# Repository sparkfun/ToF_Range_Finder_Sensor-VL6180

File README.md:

SparkFun ToF Range Finder Sensor-VL6180
=========================================

[*SparkFun ToF Range Finder Sensor-VL6180 (SEN-12785)*](https://www.sparkfun.com/products/12785)

This is the SparkFun “Time-of-Flight” Range Finder, a sensor board for the VL6180 distance sensor. 
Unlike most distance sensors that rely on reflected light intensity or reflected angles to determine range, 
the VL6180 uses a precise clock to measure the time it takes light to bounce back from a surface.

Repository Contents
-------------------
* **/Hardware** - All Eagle design files (.brd, .sch)
* **/Libraries** - All Arduino libraries and board examples
* **/Production** - Test bed files and production panel files

Documentation
--------------
* **[Library](https://github.com/sparkfun/SparkFun_ToF_Range_Finder-VL6180_Arduino_Library)** - Arduino library for the VL6180.
* **[Hookup Guide](https://learn.sparkfun.com/tutorials/vl6180-hookup-guide)** - Basic hookup guide for the VL6180.
* **[SparkFun Fritzing repo](https://github.com/sparkfun/Fritzing_Parts)** - Fritzing diagrams for SparkFun products.
* **[SparkFun 3D Model repo](https://github.com/sparkfun/3D_Models)** - 3D models of SparkFun products. 

License Information
-------------------
This product is _**open source**_! 

The **hardware** is released under [Creative Commons ShareAlike 4.0 International](https://creativecommons.org/licenses/by-sa/4.0/).

The **code** is beerware; if you see me (or any other SparkFun employee) at the local, and you've found our code helpful, please buy us a round!

Please use, reuse, and modify these files as you see fit. Please maintain attribution to SparkFun Electronics and release anything derivative under the same license.

Distributed as-is; no warranty is given.

- Your friends at SparkFun.

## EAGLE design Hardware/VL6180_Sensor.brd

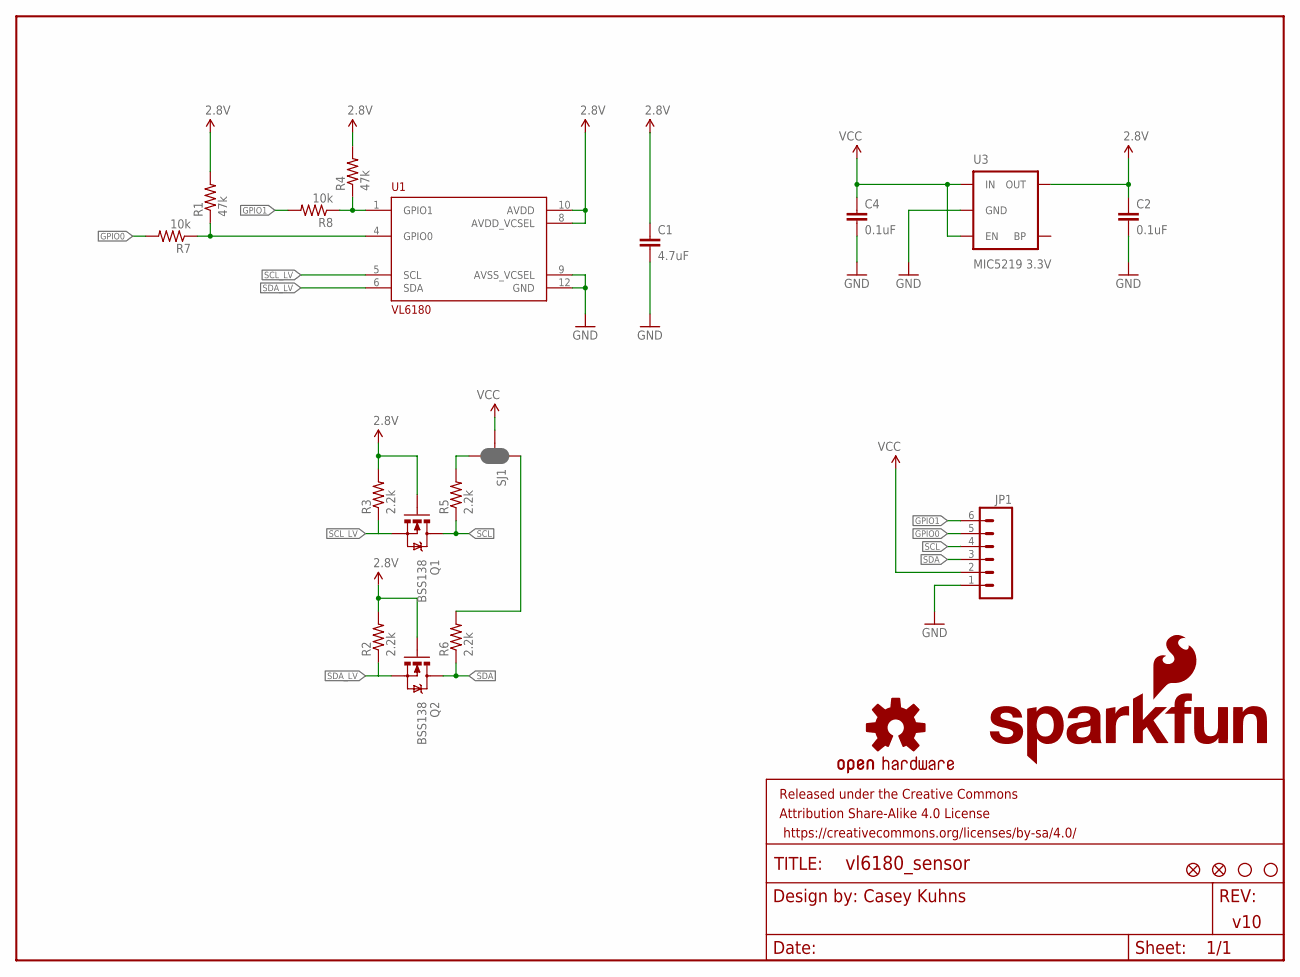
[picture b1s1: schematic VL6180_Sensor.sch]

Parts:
C1: 4.7uF; 0603-CAP
C2, C4: 0.1uF; 0603-CAP
FID1, FID2: FIDUCIAL1X2; FIDUCIAL-1X2
FRAME1: FRAME-LETTER; CREATIVE_COMMONS
JP1: M06SIP; 1X06
LOGO1: SFE_LOGO_NAME_FLAME.1_INCH; SFE_LOGO_NAME_FLAME_.1
LOGO2: OSHW-LOGOS; OSHW-LOGO-S
Q1, Q2: BSS138; SOT23
R1, R4: 47k; 0603-RES
R2, R3, R5, R6: 2.2k; 0603-RES
R7, R8: 10k; 0603-RES
SJ1: JUMPER-PAD-3-NC_BY_PASTE; PAD-JUMPER-3-NC_BY_PASTE_YES_SILK_FULL_BOX
STANDOFF1, STANDOFF2: STAND-OFF
U1: VL6180
U3: MIC5219 3.3V; SOT23-5

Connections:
2.8V: C1.1, C2.1, Q1.1 (G), Q2.1 (G), R1.2, R2.2, R3.2, R4.2, U1.8 (AVDD_VCSEL), U1.10 (AVDD), U3.5 (OUT)
GND: C1.2, C2.2, C4.2, JP1.1, U1.9 (AVSS_VCSEL), U1.12 (GND), U3.2 (GND)
GPIO0: JP1.5, R7.2
GPIO1: JP1.6, R8.2
unnamed: R6.2, SJ1.1
unnamed: R5.2, SJ1.3
unnamed: R1.1, R7.1, U1.4 (GPIO0)
unnamed: R4.1, R8.1, U1.1 (GPIO1)
SCL: JP1.4, Q1.3 (D), R5.1
SCL_LV: Q1.2 (S), R3.1, U1.5 (SCL)
SDA: JP1.3, Q2.3 (D), R6.1
SDA_LV: Q2.2 (S), R2.1, U1.6 (SDA)
VCC: C4.1, JP1.2, SJ1.2, U3.1 (IN), U3.3 (EN)

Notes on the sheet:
Casey Kuhns
v10

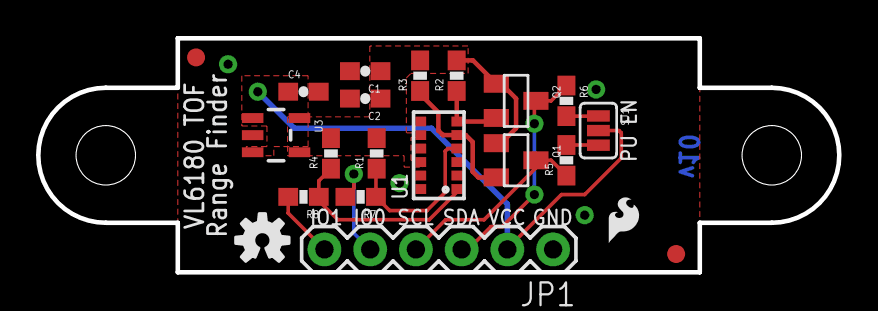
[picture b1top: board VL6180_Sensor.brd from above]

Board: 2 copper layers, 44.5 x 13.0 mm, 25 parts (1 on the bottom side), 13 nets.

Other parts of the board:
U$2: SFE_LOGO_FLAME_.1

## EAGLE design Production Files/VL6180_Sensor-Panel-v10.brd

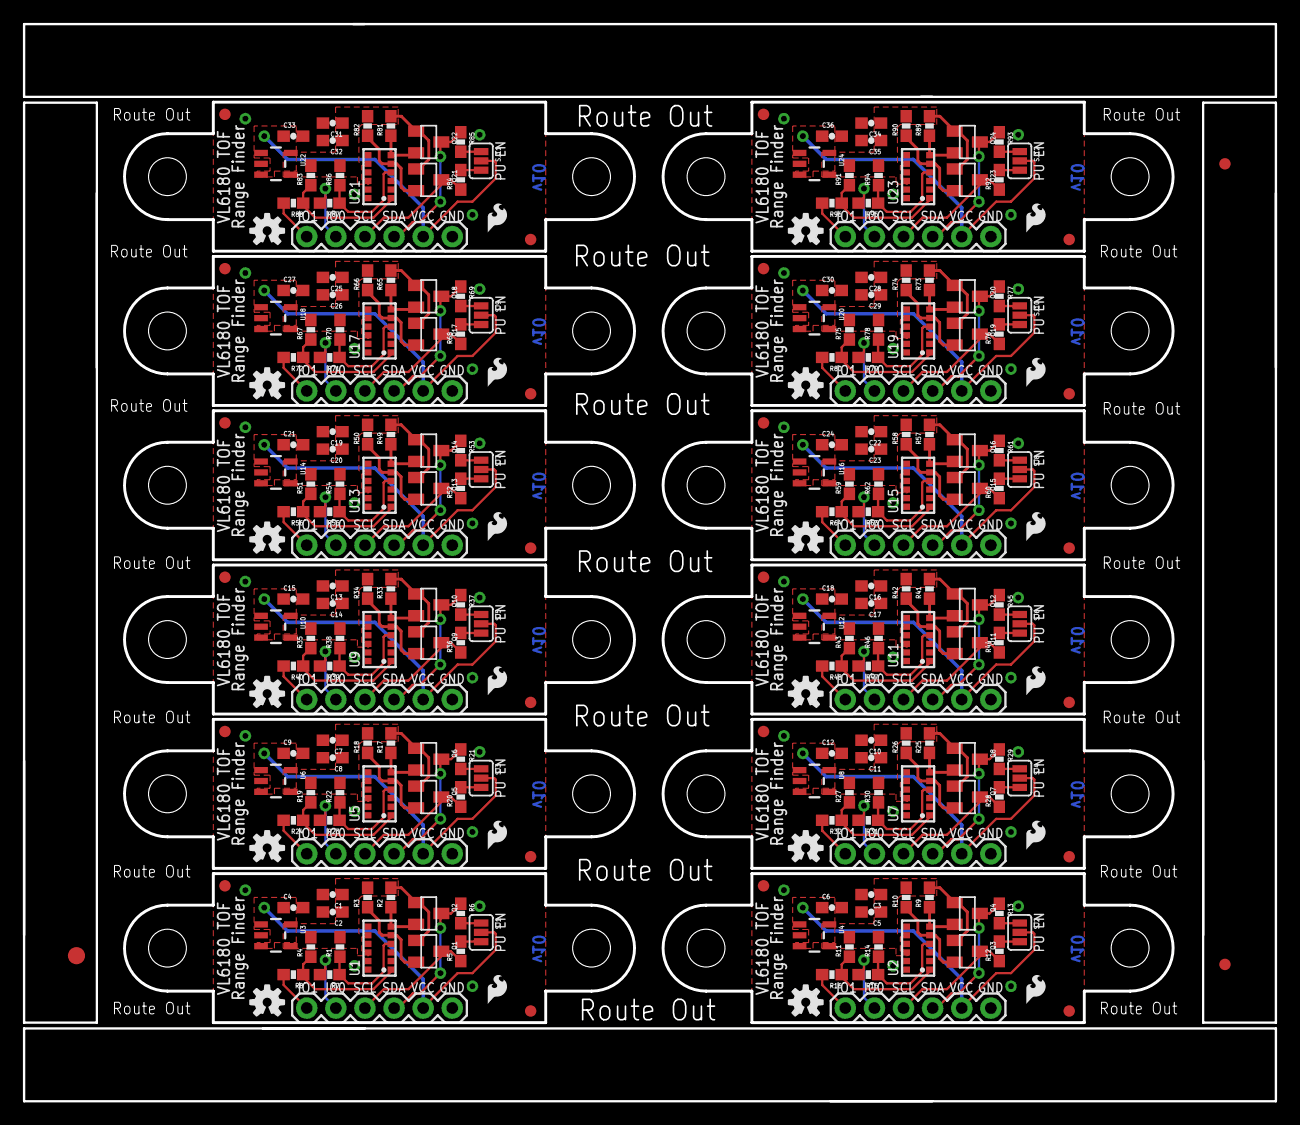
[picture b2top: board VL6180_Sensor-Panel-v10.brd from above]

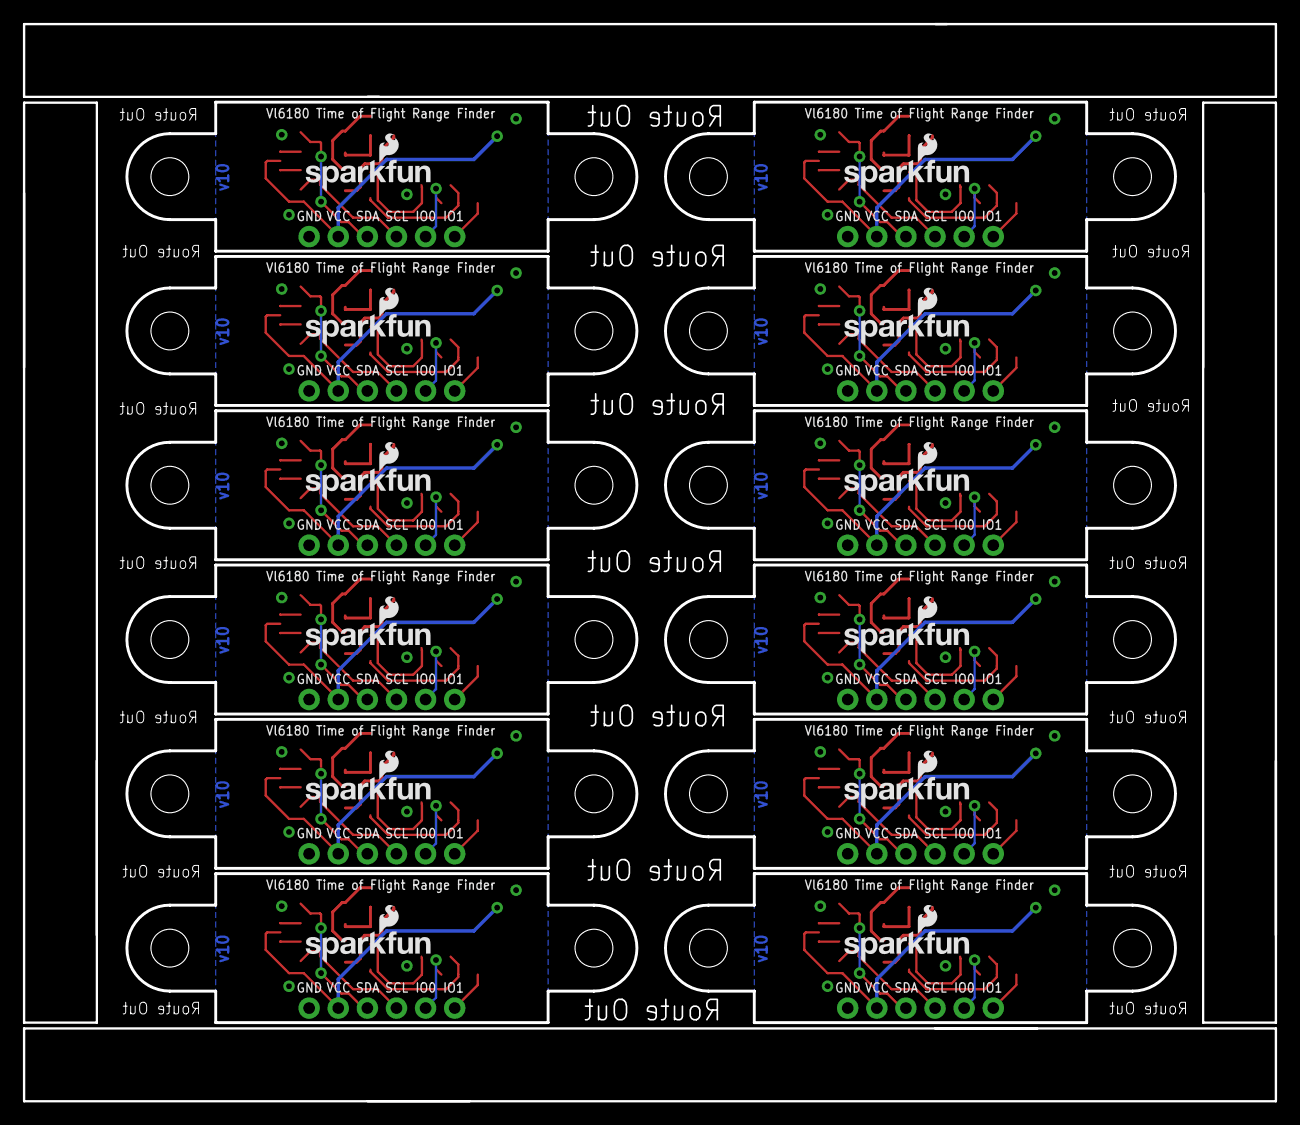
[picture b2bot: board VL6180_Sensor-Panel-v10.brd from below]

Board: 2 copper layers, 109.2 x 93.9 mm, 291 parts (12 on the bottom side), 156 nets.

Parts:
C1, C3, C7, C10, C13, C16, C19, C22, C25, C28, C31, C34: 4.7uF; 0603-CAP
C2, C4, C5, C6, C8, C9, C11, C12, C14, C15, C17, C18, C20, C21, C23, C24, C26, C27, C29, C30, C32, C33, C35, C36: 0.1uF; 0603-CAP
E$1: FIDUCIAL-1.5X3
E$4, E$5: FIDUCIAL-1X2
FID1, FID2, FID3, FID4, FID5, FID6, FID7, FID8, FID9, FID10, FID11, FID12, FID13, FID14, FID15, FID16, FID17, FID18, FID19, FID20, FID21, FID22, FID23, FID24: FIDUCIAL1X2; FIDUCIAL-1X2
JP1, JP2, JP3, JP4, JP5, JP6, JP7, JP8, JP9, JP10, JP11, JP12: 1X06
LOGO1, LOGO3, LOGO5, LOGO7, LOGO9, LOGO11, LOGO13, LOGO15, LOGO17, LOGO19, LOGO21, LOGO23: SFE_LOGO_NAME_FLAME.1_INCH; SFE_LOGO_NAME_FLAME_.1
LOGO2, LOGO4, LOGO6, LOGO8, LOGO10, LOGO12, LOGO14, LOGO16, LOGO18, LOGO20, LOGO22, LOGO24: OSHW-LOGOS; OSHW-LOGO-S
Q1, Q2, Q3, Q4, Q5, Q6, Q7, Q8, Q9, Q10, Q11, Q12, Q13, Q14, Q15, Q16, Q17, Q18, Q19, Q20, Q21, Q22, Q23, Q24: BSS138; SOT23
R1, R4, R11, R14, R19, R22, R27, R30, R35, R38, R43, R46, R51, R54, R59, R62, R67, R70, R75, R78, R83, R86, R91, R94: 47k; 0603-RES
R2, R3, R5, R6, R9, R10, R12, R13, R17, R18, R20, R21, R25, R26, R28, R29, R33, R34, R36, R37, R41, R42, R44, R45, R49, R50, R52, R53, R57, R58, R60, R61, R65, R66, R68, R69, R73, R74, R76, R77, R81, R82, R84, R85, R89, R90, R92, R93: 2.2k; 0603-RES
R7, R8, R15, R16, R23, R24, R31, R32, R39, R40, R47, R48, R55, R56, R63, R64, R71, R72, R79, R80, R87, R88, R95, R96: 10k; 0603-RES
SJ1, SJ2, SJ3, SJ4, SJ5, SJ6, SJ7, SJ8, SJ9, SJ10, SJ11, SJ12: PAD-JUMPER-3-NC_BY_PASTE_YES_SILK_FULL_BOX
STANDOFF1, STANDOFF2, STANDOFF3, STANDOFF4, STANDOFF5, STANDOFF6, STANDOFF7, STANDOFF8, STANDOFF9, STANDOFF10, STANDOFF11, STANDOFF12, STANDOFF13, STANDOFF14, STANDOFF15, STANDOFF16, STANDOFF17, STANDOFF18, STANDOFF19, STANDOFF20, STANDOFF21, STANDOFF22, STANDOFF23, STANDOFF24: STAND-OFF
U1, U2, U5, U7, U9, U11, U13, U15, U17, U19, U21, U23: VL6180
U3, U4, U6, U8, U10, U12, U14, U16, U18, U20, U22, U24: MIC5219 3.3V; SOT23-5
U$1, U$2, U$3, U$4, U$5, U$6, U$7, U$8, U$9, U$10, U$11, U$12: SFE_LOGO_FLAME_.1

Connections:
2.8V: C1.1, C2.1, Q1.1, Q2.1, R1.2, R2.2, R3.2, R4.2, U1.8, U1.10, U3.5
2.8V1: C3.1, C5.1, Q3.1, Q4.1, R9.2, R10.2, R11.2, R14.2, U2.8, U2.10, U4.5
2.8V2: C7.1, C8.1, Q5.1, Q6.1, R17.2, R18.2, R19.2, R22.2, U5.8, U5.10, U6.5
2.8V3: C10.1, C11.1, Q7.1, Q8.1, R25.2, R26.2, R27.2, R30.2, U7.8, U7.10, U8.5
2.8V4: C13.1, C14.1, Q9.1, Q10.1, R33.2, R34.2, R35.2, R38.2, U9.8, U9.10, U10.5
2.8V5: C16.1, C17.1, Q11.1, Q12.1, R41.2, R42.2, R43.2, R46.2, U11.8, U11.10, U12.5
2.8V6: C19.1, C20.1, Q13.1, Q14.1, R49.2, R50.2, R51.2, R54.2, U13.8, U13.10, U14.5
2.8V7: C22.1, C23.1, Q15.1, Q16.1, R57.2, R58.2, R59.2, R62.2, U15.8, U15.10, U16.5
2.8V8: C25.1, C26.1, Q17.1, Q18.1, R65.2, R66.2, R67.2, R70.2, U17.8, U17.10, U18.5
2.8V9: C28.1, C29.1, Q19.1, Q20.1, R73.2, R74.2, R75.2, R78.2, U19.8, U19.10, U20.5
2.8V10: C31.1, C32.1, Q21.1, Q22.1, R81.2, R82.2, R83.2, R86.2, U21.8, U21.10, U22.5
2.8V11: C34.1, C35.1, Q23.1, Q24.1, R89.2, R90.2, R91.2, R94.2, U23.8, U23.10, U24.5
GND: C1.2, C2.2, C4.2, JP1.1, U1.9, U1.12, U3.2
GND1: C3.2, C5.2, C6.2, JP2.1, U2.9, U2.12, U4.2
GND2: C7.2, C8.2, C9.2, JP3.1, U5.9, U5.12, U6.2
GND3: C10.2, C11.2, C12.2, JP4.1, U7.9, U7.12, U8.2
GND4: C13.2, C14.2, C15.2, JP5.1, U9.9, U9.12, U10.2
GND5: C16.2, C17.2, C18.2, JP6.1, U11.9, U11.12, U12.2
GND6: C19.2, C20.2, C21.2, JP7.1, U13.9, U13.12, U14.2
GND7: C22.2, C23.2, C24.2, JP8.1, U15.9, U15.12, U16.2
GND8: C25.2, C26.2, C27.2, JP9.1, U17.9, U17.12, U18.2
GND9: C28.2, C29.2, C30.2, JP10.1, U19.9, U19.12, U20.2
GND10: C31.2, C32.2, C33.2, JP11.1, U21.9, U21.12, U22.2
GND11: C34.2, C35.2, C36.2, JP12.1, U23.9, U23.12, U24.2
GPIO0: JP1.5, R7.2
GPIO1: JP1.6, R8.2
GPIO2: JP2.5, R15.2
GPIO3: JP2.6, R16.2
GPIO4: JP3.5, R23.2
GPIO5: JP3.6, R24.2
GPIO6: JP4.5, R31.2
GPIO7: JP4.6, R32.2
GPIO8: JP5.5, R39.2
GPIO9: JP5.6, R40.2
GPIO10: JP6.5, R47.2
GPIO11: JP6.6, R48.2
GPIO12: JP7.5, R55.2
GPIO13: JP7.6, R56.2
GPIO14: JP8.5, R63.2
GPIO15: JP8.6, R64.2
GPIO16: JP9.5, R71.2
GPIO17: JP9.6, R72.2
GPIO18: JP10.5, R79.2
GPIO19: JP10.6, R80.2
GPIO20: JP11.5, R87.2
GPIO21: JP11.6, R88.2
GPIO22: JP12.5, R95.2
GPIO23: JP12.6, R96.2
unnamed: R13.2, SJ2.1
unnamed: R6.2, SJ1.1
unnamed: R5.2, SJ1.3
unnamed: R12.2, SJ2.3
unnamed: R14.1, R15.1, U2.4
unnamed: R11.1, R16.1, U2.1
unnamed: R21.2, SJ3.1
unnamed: R20.2, SJ3.3
unnamed: R22.1, R23.1, U5.4
unnamed: R19.1, R24.1, U5.1
unnamed: R29.2, SJ4.1
unnamed: R28.2, SJ4.3
unnamed: R30.1, R31.1, U7.4
unnamed: R27.1, R32.1, U7.1
unnamed: R37.2, SJ5.1
unnamed: R36.2, SJ5.3
unnamed: R38.1, R39.1, U9.4
unnamed: R35.1, R40.1, U9.1
unnamed: R45.2, SJ6.1
unnamed: R44.2, SJ6.3
unnamed: R46.1, R47.1, U11.4
unnamed: R43.1, R48.1, U11.1
unnamed: R53.2, SJ7.1
unnamed: R52.2, SJ7.3
unnamed: R54.1, R55.1, U13.4
unnamed: R51.1, R56.1, U13.1
unnamed: R61.2, SJ8.1
unnamed: R60.2, SJ8.3
unnamed: R62.1, R63.1, U15.4
unnamed: R59.1, R64.1, U15.1
unnamed: R69.2, SJ9.1
unnamed: R68.2, SJ9.3
unnamed: R70.1, R71.1, U17.4
unnamed: R67.1, R72.1, U17.1
unnamed: R77.2, SJ10.1
unnamed: R76.2, SJ10.3
unnamed: R78.1, R79.1, U19.4
unnamed: R75.1, R80.1, U19.1
unnamed: R85.2, SJ11.1
unnamed: R84.2, SJ11.3
unnamed: R86.1, R87.1, U21.4
unnamed: R83.1, R88.1, U21.1
unnamed: R93.2, SJ12.1
unnamed: R92.2, SJ12.3
unnamed: R94.1, R95.1, U23.4
unnamed: R91.1, R96.1, U23.1
unnamed: R1.1, R7.1, U1.4
unnamed: R4.1, R8.1, U1.1
SCL: JP1.4, Q1.3, R5.1
SCL1: JP2.4, Q3.3, R12.1
SCL2: JP3.4, Q5.3, R20.1
SCL3: JP4.4, Q7.3, R28.1
SCL4: JP5.4, Q9.3, R36.1
SCL5: JP6.4, Q11.3, R44.1
SCL6: JP7.4, Q13.3, R52.1
SCL7: JP8.4, Q15.3, R60.1
SCL8: JP9.4, Q17.3, R68.1
SCL9: JP10.4, Q19.3, R76.1
SCL10: JP11.4, Q21.3, R84.1
SCL11: JP12.4, Q23.3, R92.1
SCL_LV: Q1.2, R3.1, U1.5
SCL_LV1: Q3.2, R10.1, U2.5
SCL_LV2: Q5.2, R18.1, U5.5
SCL_LV3: Q7.2, R26.1, U7.5
SCL_LV4: Q9.2, R34.1, U9.5
SCL_LV5: Q11.2, R42.1, U11.5
SCL_LV6: Q13.2, R50.1, U13.5
SCL_LV7: Q15.2, R58.1, U15.5
SCL_LV8: Q17.2, R66.1, U17.5
SCL_LV9: Q19.2, R74.1, U19.5
SCL_LV10: Q21.2, R82.1, U21.5
SCL_LV11: Q23.2, R90.1, U23.5
SDA: JP1.3, Q2.3, R6.1
SDA1: JP2.3, Q4.3, R13.1
SDA2: JP3.3, Q6.3, R21.1
SDA3: JP4.3, Q8.3, R29.1
SDA4: JP5.3, Q10.3, R37.1
SDA5: JP6.3, Q12.3, R45.1
SDA6: JP7.3, Q14.3, R53.1
SDA7: JP8.3, Q16.3, R61.1
SDA8: JP9.3, Q18.3, R69.1
SDA9: JP10.3, Q20.3, R77.1
SDA10: JP11.3, Q22.3, R85.1
SDA11: JP12.3, Q24.3, R93.1
SDA_LV: Q2.2, R2.1, U1.6
SDA_LV1: Q4.2, R9.1, U2.6
SDA_LV2: Q6.2, R17.1, U5.6
SDA_LV3: Q8.2, R25.1, U7.6
SDA_LV4: Q10.2, R33.1, U9.6
SDA_LV5: Q12.2, R41.1, U11.6
SDA_LV6: Q14.2, R49.1, U13.6
SDA_LV7: Q16.2, R57.1, U15.6
SDA_LV8: Q18.2, R65.1, U17.6
SDA_LV9: Q20.2, R73.1, U19.6
SDA_LV10: Q22.2, R81.1, U21.6
SDA_LV11: Q24.2, R89.1, U23.6
VCC: C4.1, JP1.2, SJ1.2, U3.1, U3.3
VCC1: C6.1, JP2.2, SJ2.2, U4.1, U4.3
VCC2: C9.1, JP3.2, SJ3.2, U6.1, U6.3
VCC3: C12.1, JP4.2, SJ4.2, U8.1, U8.3
VCC4: C15.1, JP5.2, SJ5.2, U10.1, U10.3
VCC5: C18.1, JP6.2, SJ6.2, U12.1, U12.3
VCC6: C21.1, JP7.2, SJ7.2, U14.1, U14.3
VCC7: C24.1, JP8.2, SJ8.2, U16.1, U16.3
VCC8: C27.1, JP9.2, SJ9.2, U18.1, U18.3
VCC9: C30.1, JP10.2, SJ10.2, U20.1, U20.3
VCC10: C33.1, JP11.2, SJ11.2, U22.1, U22.3
VCC11: C36.1, JP12.2, SJ12.2, U24.1, U24.3

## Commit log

2015-02-10 initial commit, cleanup
2015-02-13 Adding product info to README, fixing directory names
2015-03-23 Updating VL6180 library path
2015-05-14 Fixing naming conventions, adding README info
2015-05-14 Squashed 'Libraries/Arduino/' content from commit dd6cce0
    git-subtree-dir: Libraries/Arduino
    git-subtree-split: dd6cce03c074b9068238a3e29b15535ec5eadf2b
2018-09-17 Correcting Syntax
    Corrected unreachable code in the getDistance method.

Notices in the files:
parts and their libraries:
SparkFun-Aesthetics: Licensing: CC v3.0 Share-Alike You are welcome to use this library for commercial purposes.
SparkFun-Aesthetics: Released under the Creative Commons Attribution Share-Alike 4.0 License
SparkFun-Aesthetics: Released under the Creative Commons
